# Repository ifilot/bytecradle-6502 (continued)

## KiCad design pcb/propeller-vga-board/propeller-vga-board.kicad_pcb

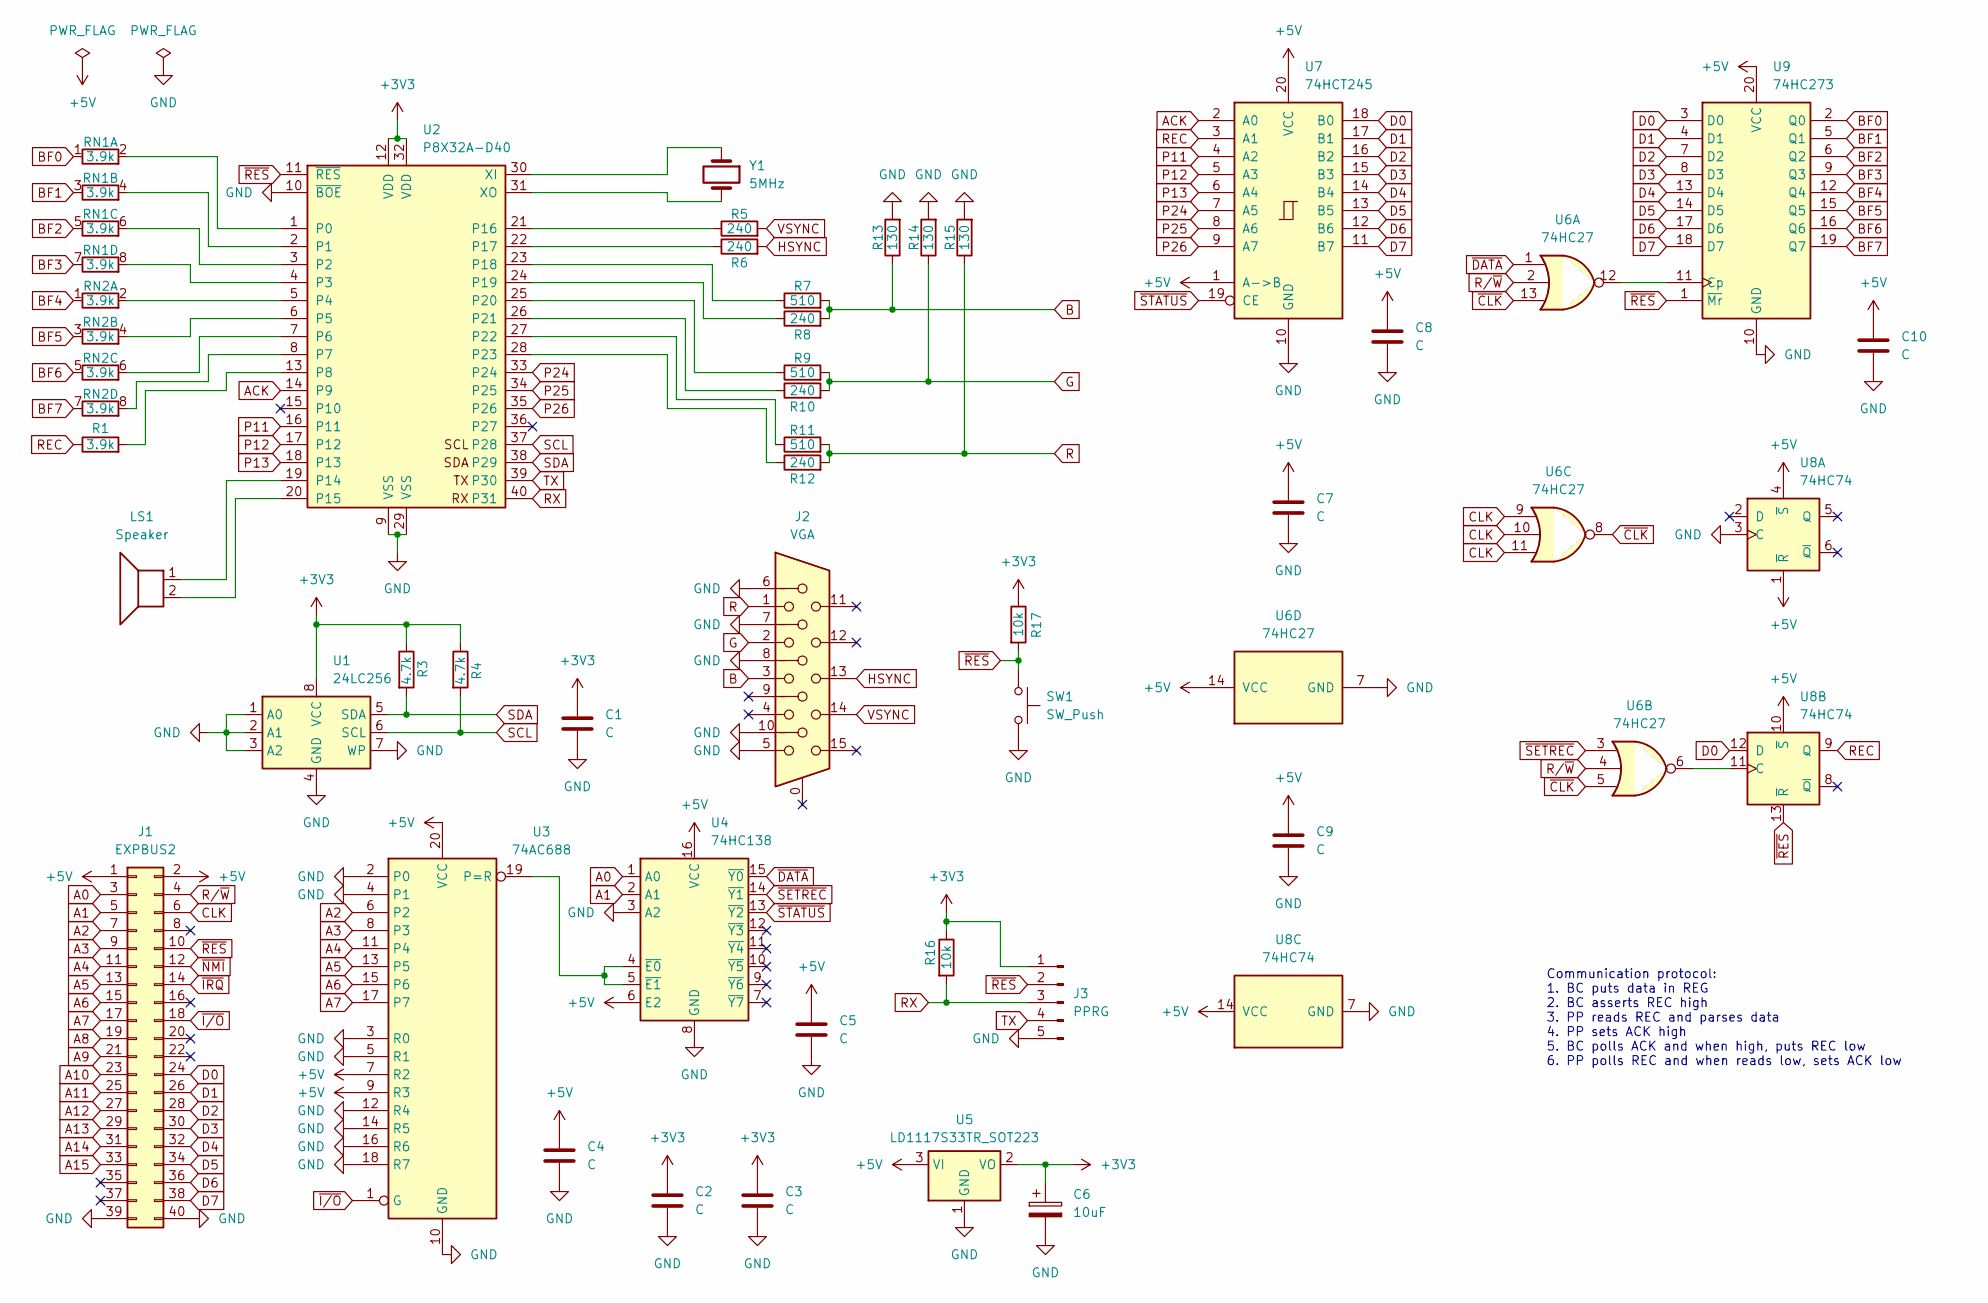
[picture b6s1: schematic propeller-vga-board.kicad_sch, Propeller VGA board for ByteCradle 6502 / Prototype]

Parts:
C1, C2, C3, C4, C5, C7, C8, C9, C10: C; C_Disc_D5.0mm_W2.5mm_P5.00mm
C6: 10uF; CP_Radial_D5.0mm_P2.50mm
J1: EXPBUS2; PinSocket_2x20_P2.54mm_Horizontal
J2: VGA; 618015330923
J3: PPRG; PinSocket_1x05_P2.54mm_Vertical
LS1: Speaker; MagneticBuzzer_ProSignal_ABI-009-RC
R1: 3.9k; R_Axial_DIN0207_L6.3mm_D2.5mm_P7.62mm_Horizontal
R3, R4: 4.7k; R_Axial_DIN0207_L6.3mm_D2.5mm_P7.62mm_Horizontal
R5, R6, R8, R10, R12: 240; R_Axial_DIN0207_L6.3mm_D2.5mm_P7.62mm_Horizontal
R7, R9, R11: 510; R_Axial_DIN0207_L6.3mm_D2.5mm_P7.62mm_Horizontal
R13, R14, R15: 130; R_Axial_DIN0207_L6.3mm_D2.5mm_P7.62mm_Horizontal
R16, R17: 10k; R_Axial_DIN0207_L6.3mm_D2.5mm_P7.62mm_Horizontal
RN1, RN2: 3.9k; R_Array_SIP8
SW1: SW_Push; SW_PUSH_6mm
U1: 24LC256; DIP-8_W7.62mm_Socket
U2: P8X32A-D40; DIP-40_W15.24mm_Socket
U3: 74AC688; DIP-20_W7.62mm_Socket
U4: 74HC138; DIP-16_W7.62mm_Socket
U5: LD1117S33TR_SOT223; SOT-223-3_TabPin2
U6: 74HC27; DIP-14_W7.62mm_Socket
U7: 74HCT245; DIP-20_W7.62mm_Socket
U8: 74HC74; DIP-14_W7.62mm_Socket
U9: 74HC273; DIP-20_W7.62mm_Socket
Y1: 5MHz; Crystal_HC49-4H_Vertical

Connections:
+3V3: C1.1, C2.1, C3.1, C6.1, J3.1, R3.1, R4.1, R16.1, R17.1, U1.8 (VCC), U2.12 (VDD), U2.32 (VDD), U5.2 (VO)
+5V: C4.1, C5.1, C7.1, C8.1, C9.1, C10.1, J1.1, J1.2, U3.7 (R2), U3.9 (R3), U3.20 (VCC), U4.6 (E2), U4.16 (VCC), U5.3 (VI), U6.14 (VCC), U7.1 (A->B), U7.20 (VCC), U8.1 (~R), U8.4 (~S), U8.10 (~S), U8.14 (VCC), U9.20 (VCC)
A0: J1.3, U4.1 (A0)
A1: J1.5, U4.2 (A1)
A2: J1.7, U3.6 (P2)
A3: J1.9, U3.8 (P3)
A4: J1.11, U3.11 (P4)
A5: J1.13, U3.13 (P5)
A6: J1.15, U3.15 (P6)
A7: J1.17, U3.17 (P7)
A8: J1.19
A9: J1.21
A10: J1.23
A11: J1.25
A12: J1.27
A13: J1.29
A14: J1.31
A15: J1.33
ACK: U2.14 (P9), U7.2 (A0)
B: J2.3, R7.2, R8.2, R13.1
BF0: RN1.1 (R1.1), U9.2 (Q0)
BF1: RN1.3 (R2.1), U9.5 (Q1)
BF2: RN1.5 (R3.1), U9.6 (Q2)
BF3: RN1.7 (R4.1), U9.9 (Q3)
BF4: RN2.1 (R1.1), U9.12 (Q4)
BF5: RN2.3 (R2.1), U9.15 (Q5)
BF6: RN2.5 (R3.1), U9.16 (Q6)
BF7: RN2.7 (R4.1), U9.19 (Q7)
CLK: J1.6, U6.9, U6.10, U6.11
D0: J1.24, U7.18 (B0), U8.12 (D), U9.3 (D0)
D1: J1.26, U7.17 (B1), U9.4 (D1)
D2: J1.28, U7.16 (B2), U9.7 (D2)
D3: J1.30, U7.15 (B3), U9.8 (D3)
D4: J1.32, U7.14 (B4), U9.13 (D4)
D5: J1.34, U7.13 (B5), U9.14 (D5)
D6: J1.36, U7.12 (B6), U9.17 (D6)
D7: J1.38, U7.11 (B7), U9.18 (D7)
G: J2.2, R9.2, R10.2, R14.1
GND: C1.2, C2.2, C3.2, C4.2, C5.2, C6.2, C7.2, C8.2, C9.2, C10.2, J1.39, J1.40, J2.5, J2.6, J2.7, J2.8, J2.10, J3.5, R13.2, R14.2, R15.2, SW1.1, U1.1 (A0), U1.2 (A1), U1.3 (A2), U1.4 (GND), U1.7 (WP), U2.9 (VSS), U2.10 (~BOE), U2.29 (VSS), U3.2 (P0), U3.3 (R0), U3.4 (P1), U3.5 (R1), U3.10 (GND), U3.12 (R4), U3.14 (R5), U3.16 (R6), U3.18 (R7), U4.3 (A2), U4.8 (GND), U5.1 (GND), U6.7 (GND), U7.10 (GND), U8.3 (C), U8.7 (GND), U9.10 (GND)
HSYNC: J2.13, R6.2
unnamed: RN1.2 (R1.2), U2.1 (P0)
unnamed: RN1.4 (R2.2), U2.2 (P1)
unnamed: RN1.6 (R3.2), U2.3 (P2)
unnamed: RN1.8 (R4.2), U2.4 (P3)
unnamed: RN2.2 (R1.2), U2.5 (P4)
unnamed: RN2.4 (R2.2), U2.6 (P5)
unnamed: RN2.6 (R3.2), U2.7 (P6)
unnamed: RN2.8 (R4.2), U2.8 (P7)
unnamed: R1.2, U2.13 (P8)
unnamed: LS1.1, U2.19 (P14)
unnamed: LS1.2, U2.20 (P15)
unnamed: R5.1, U2.21 (P16)
unnamed: R6.1, U2.22 (P17)
unnamed: R7.1, U2.23 (P18)
unnamed: R8.1, U2.24 (P19)
unnamed: R9.1, U2.25 (P20)
unnamed: R10.1, U2.26 (P21)
unnamed: R11.1, U2.27 (P22)
unnamed: R12.1, U2.28 (P23)
unnamed: U2.30 (XI), Y1.1
unnamed: U2.31 (XO), Y1.2
unnamed: U3.19 (P=R), U4.4 (~E0), U4.5 (~E1)
unnamed: U6.6, U8.11 (C)
unnamed: U6.12, U9.11 (Cp)
P11: U2.16 (P11), U7.4 (A2)
P12: U2.17 (P12), U7.5 (A3)
P13: U2.18 (P13), U7.6 (A4)
P24: U2.33 (P24), U7.7 (A5)
P25: U2.34 (P25), U7.8 (A6)
P26: U2.35 (P26), U7.9 (A7)
R: J2.1, R11.2, R12.2, R15.1
REC: R1.1, U7.3 (A1), U8.9 (Q)
RX: J3.3, R16.2, U2.40 (P31)
R/~W: J1.4, U6.2, U6.4
SCL: R4.2, U1.6 (SCL), U2.37 (P28)
SDA: R3.2, U1.5 (SDA), U2.38 (P29)
TX: J3.4, U2.39 (P30)
VSYNC: J2.14, R5.2
~CLK: U6.5, U6.8, U6.13
~DATA: U4.15 (~Y0), U6.1
~IRQ: J1.14
~I/O: J1.18, U3.1 (G)
~NMI: J1.12
~RES: J1.10, J3.2, R17.2, SW1.2, U2.11 (~RES), U8.13 (~R), U9.1 (~Mr)
~SETREC: U4.14 (~Y1), U6.3
~STATUS: U4.13 (~Y2), U7.19 (CE)

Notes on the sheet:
Communication protocol: 1. BC puts data in REG 2. BC asserts REC high 3. PP reads REC and parses data 4. PP sets ACK high 5. BC polls ACK and when high, puts REC low 6. PP polls REC and when reads low, sets ACK low

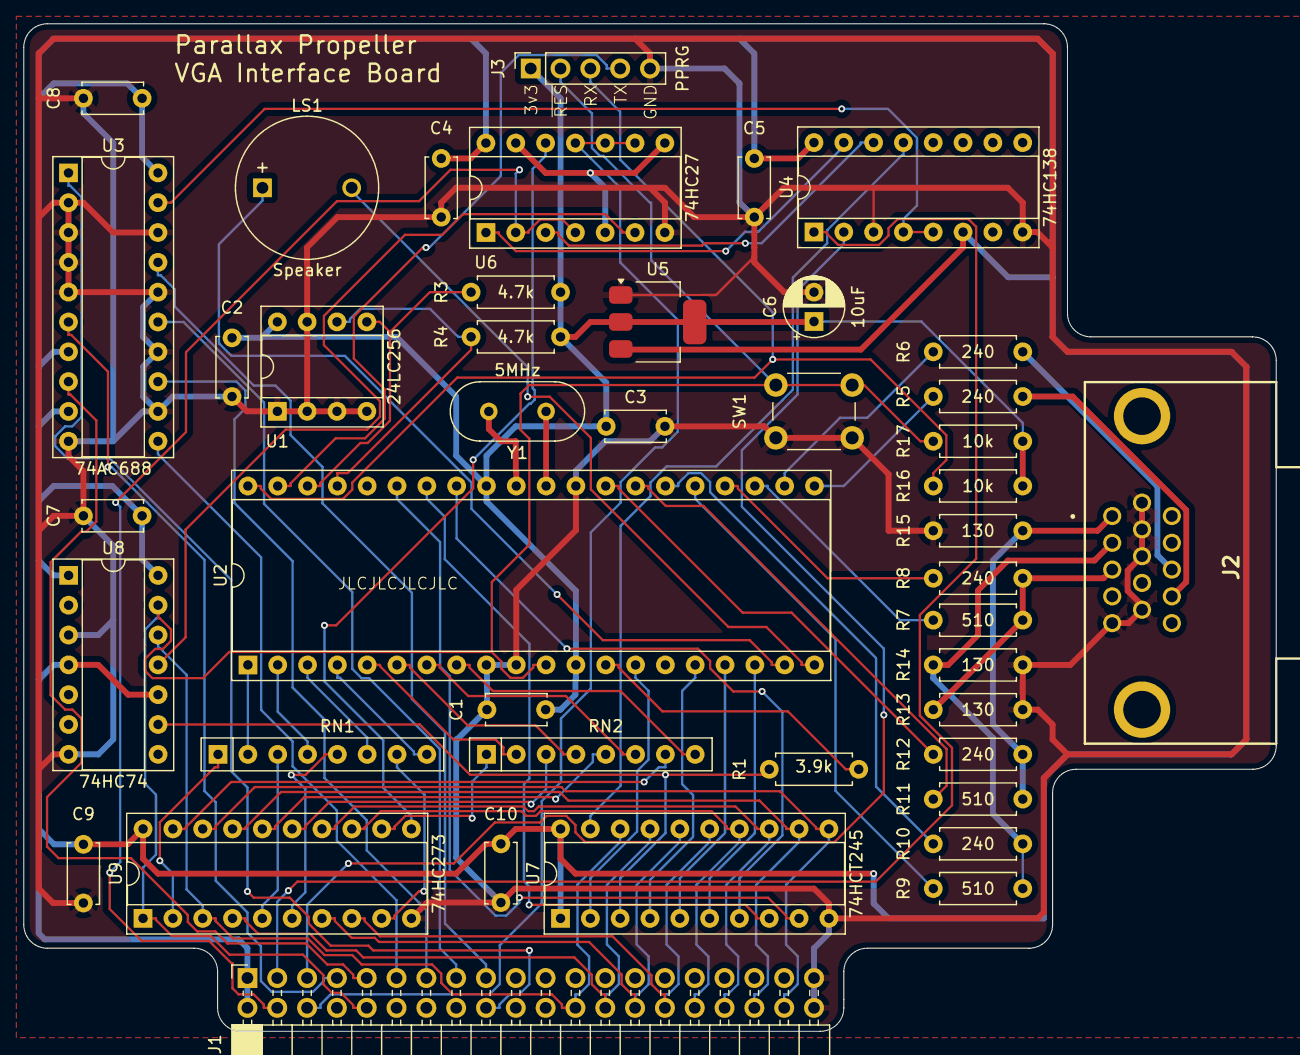
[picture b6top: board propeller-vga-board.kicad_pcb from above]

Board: 2 copper layers, 106.7 x 85.8 mm, 43 parts (0 on the bottom side), 76 nets.

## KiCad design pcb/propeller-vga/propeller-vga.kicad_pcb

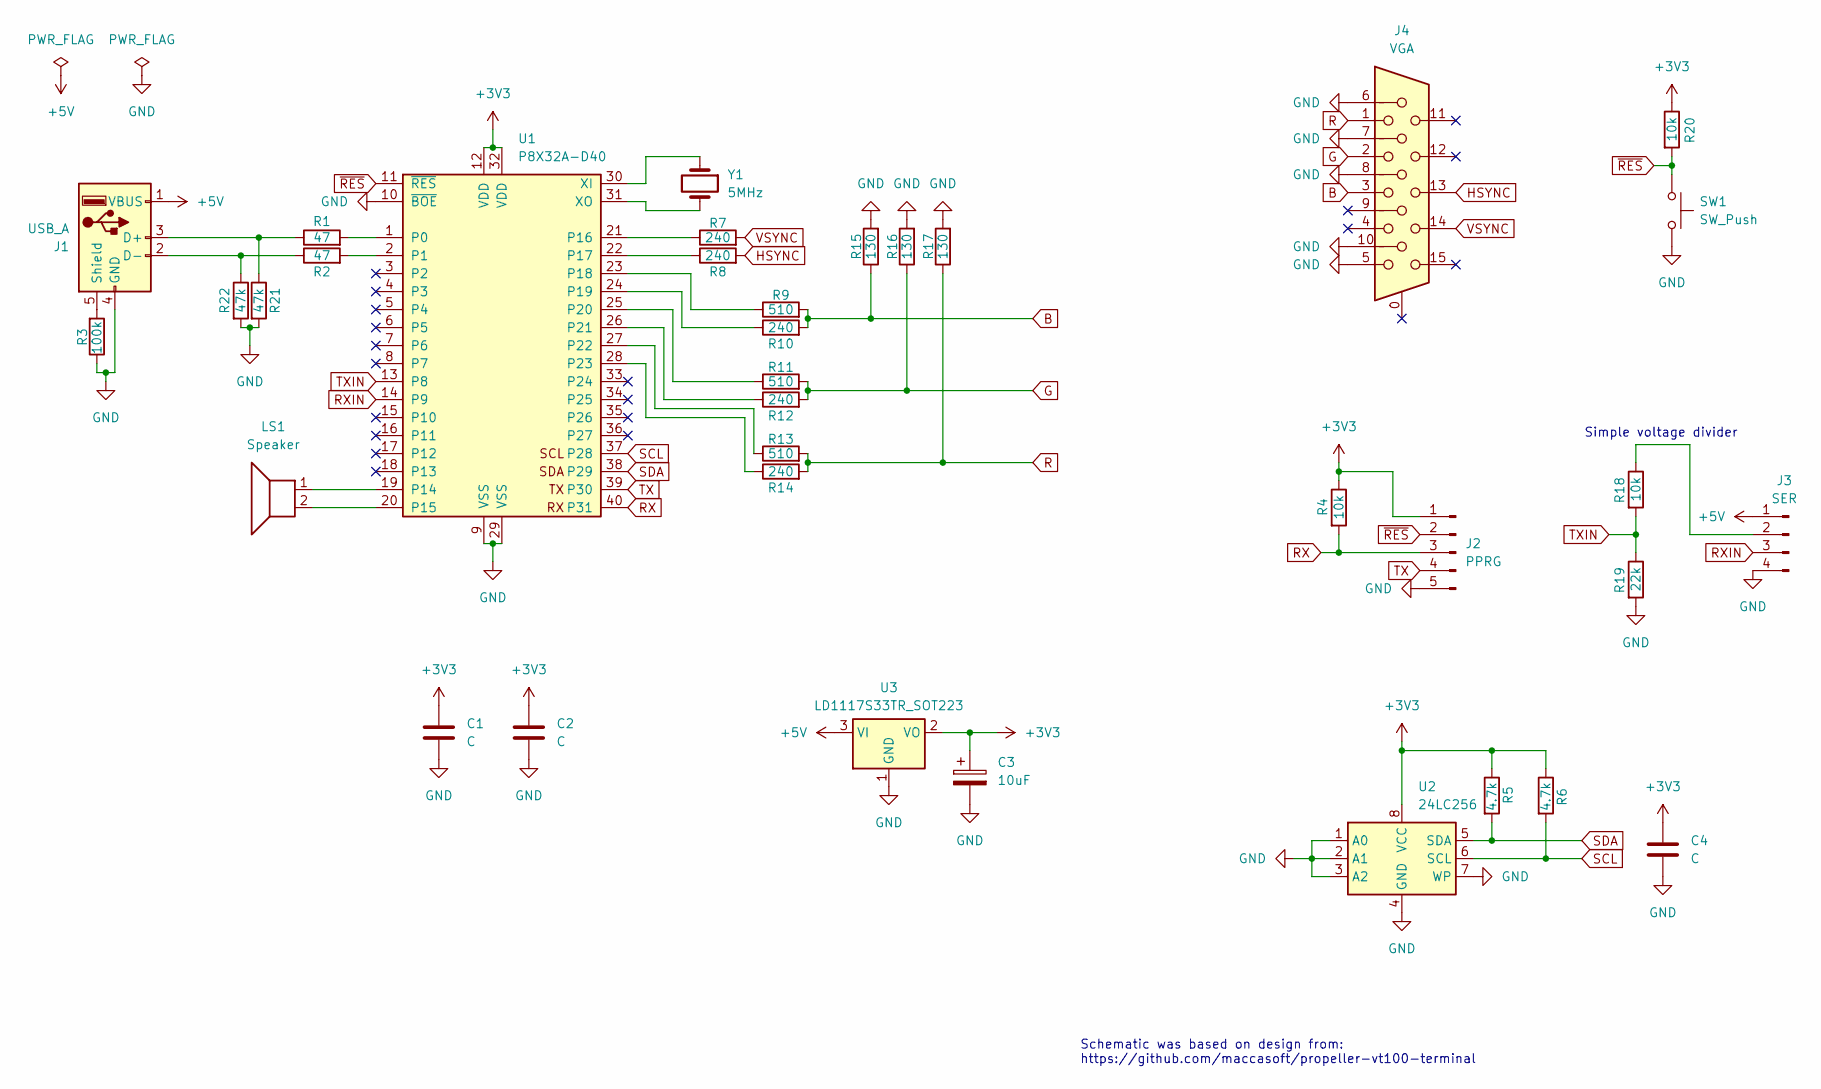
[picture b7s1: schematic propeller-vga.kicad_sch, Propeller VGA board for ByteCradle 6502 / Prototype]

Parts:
C1, C2, C4: C; C_Disc_D5.0mm_W2.5mm_P5.00mm
C3: 10uF; CP_Radial_D5.0mm_P2.50mm
J1: USB_A; USB_A_Stewart_SS-52100-001_Horizontal
J2: PPRG; PinSocket_1x05_P2.54mm_Vertical
J3: SER; PinSocket_1x04_P2.54mm_Vertical
J4: VGA; 618015330923
LS1: Speaker; MagneticBuzzer_ProSignal_ABI-009-RC
R1, R2: 47; R_Axial_DIN0207_L6.3mm_D2.5mm_P7.62mm_Horizontal
R3: 100k; R_Axial_DIN0207_L6.3mm_D2.5mm_P7.62mm_Horizontal
R4, R18, R20: 10k; R_Axial_DIN0207_L6.3mm_D2.5mm_P7.62mm_Horizontal
R5, R6: 4.7k; R_Axial_DIN0207_L6.3mm_D2.5mm_P7.62mm_Horizontal
R7, R8, R10, R12, R14: 240; R_Axial_DIN0207_L6.3mm_D2.5mm_P7.62mm_Horizontal
R9, R11, R13: 510; R_Axial_DIN0207_L6.3mm_D2.5mm_P7.62mm_Horizontal
R15, R16, R17: 130; R_Axial_DIN0207_L6.3mm_D2.5mm_P7.62mm_Horizontal
R19: 22k; R_Axial_DIN0207_L6.3mm_D2.5mm_P7.62mm_Horizontal
R21, R22: 47k; R_Axial_DIN0207_L6.3mm_D2.5mm_P7.62mm_Horizontal
SW1: SW_Push; SW_PUSH_6mm
U1: P8X32A-D40; DIP-40_W15.24mm_Socket
U2: 24LC256; DIP-8_W7.62mm_Socket
U3: LD1117S33TR_SOT223; SOT-223-3_TabPin2
Y1: 5MHz; Crystal_HC49-4H_Vertical

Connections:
+3V3: C1.1, C2.1, C3.1, C4.1, J2.1, R4.1, R5.1, R6.1, R20.1, U1.12 (VDD), U1.32 (VDD), U2.8 (VCC), U3.2 (VO)
+5V: J1.1 (VBUS), J3.1, U3.3 (VI)
B: J4.3, R9.2, R10.2, R15.1
G: J4.2, R11.2, R12.2, R16.1
GND: C1.2, C2.2, C3.2, C4.2, J1.4 (GND), J2.5, J3.4, J4.5, J4.6, J4.7, J4.8, J4.10, R3.1, R15.2, R16.2, R17.2, R19.2, R21.2, R22.2, SW1.1, U1.9 (VSS), U1.10 (~BOE), U1.29 (VSS), U2.1 (A0), U2.2 (A1), U2.3 (A2), U2.4 (GND), U2.7 (WP), U3.1 (GND)
HSYNC: J4.13, R8.2
unnamed: J1.3 (D+), R1.1, R21.1
unnamed: J1.2 (D-), R2.1, R22.1
unnamed: J1.5 (Shield), R3.2
unnamed: J3.2, R18.1
unnamed: R1.2, U1.1 (P0)
unnamed: R2.2, U1.2 (P1)
unnamed: LS1.1, U1.19 (P14)
unnamed: LS1.2, U1.20 (P15)
unnamed: R7.1, U1.21 (P16)
unnamed: R8.1, U1.22 (P17)
unnamed: R9.1, U1.23 (P18)
unnamed: R10.1, U1.24 (P19)
unnamed: R11.1, U1.25 (P20)
unnamed: R12.1, U1.26 (P21)
unnamed: R13.1, U1.27 (P22)
unnamed: R14.1, U1.28 (P23)
unnamed: U1.30 (XI), Y1.1
unnamed: U1.31 (XO), Y1.2
R: J4.1, R13.2, R14.2, R17.1
RX: J2.3, R4.2, U1.40 (P31)
RXIN: J3.3, U1.14 (P9)
SCL: R6.2, U1.37 (P28), U2.6 (SCL)
SDA: R5.2, U1.38 (P29), U2.5 (SDA)
TX: J2.4, U1.39 (P30)
TXIN: R18.2, R19.1, U1.13 (P8)
VSYNC: J4.14, R7.2
~RES: J2.2, R20.2, SW1.2, U1.11 (~RES)

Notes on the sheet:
Schematic was based on design from: https://github.com/maccasoft/propeller-vt100-terminal
Simple voltage divider

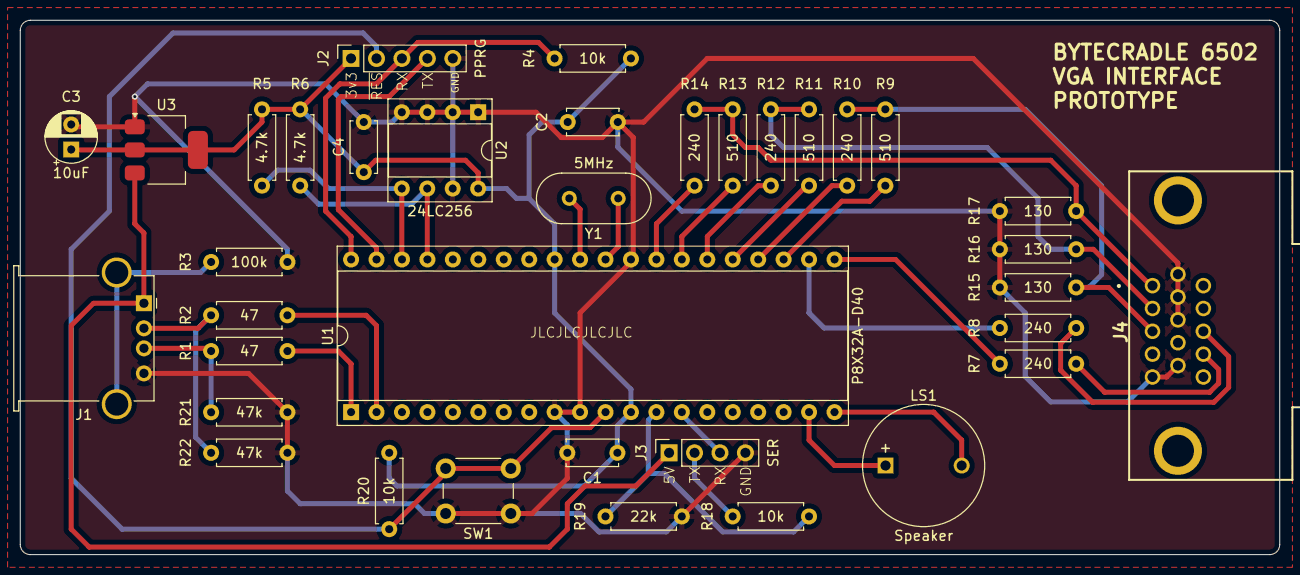
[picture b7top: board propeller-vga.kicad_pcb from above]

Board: 2 copper layers, 125.7 x 53.3 mm, 36 parts (0 on the bottom side), 33 nets.

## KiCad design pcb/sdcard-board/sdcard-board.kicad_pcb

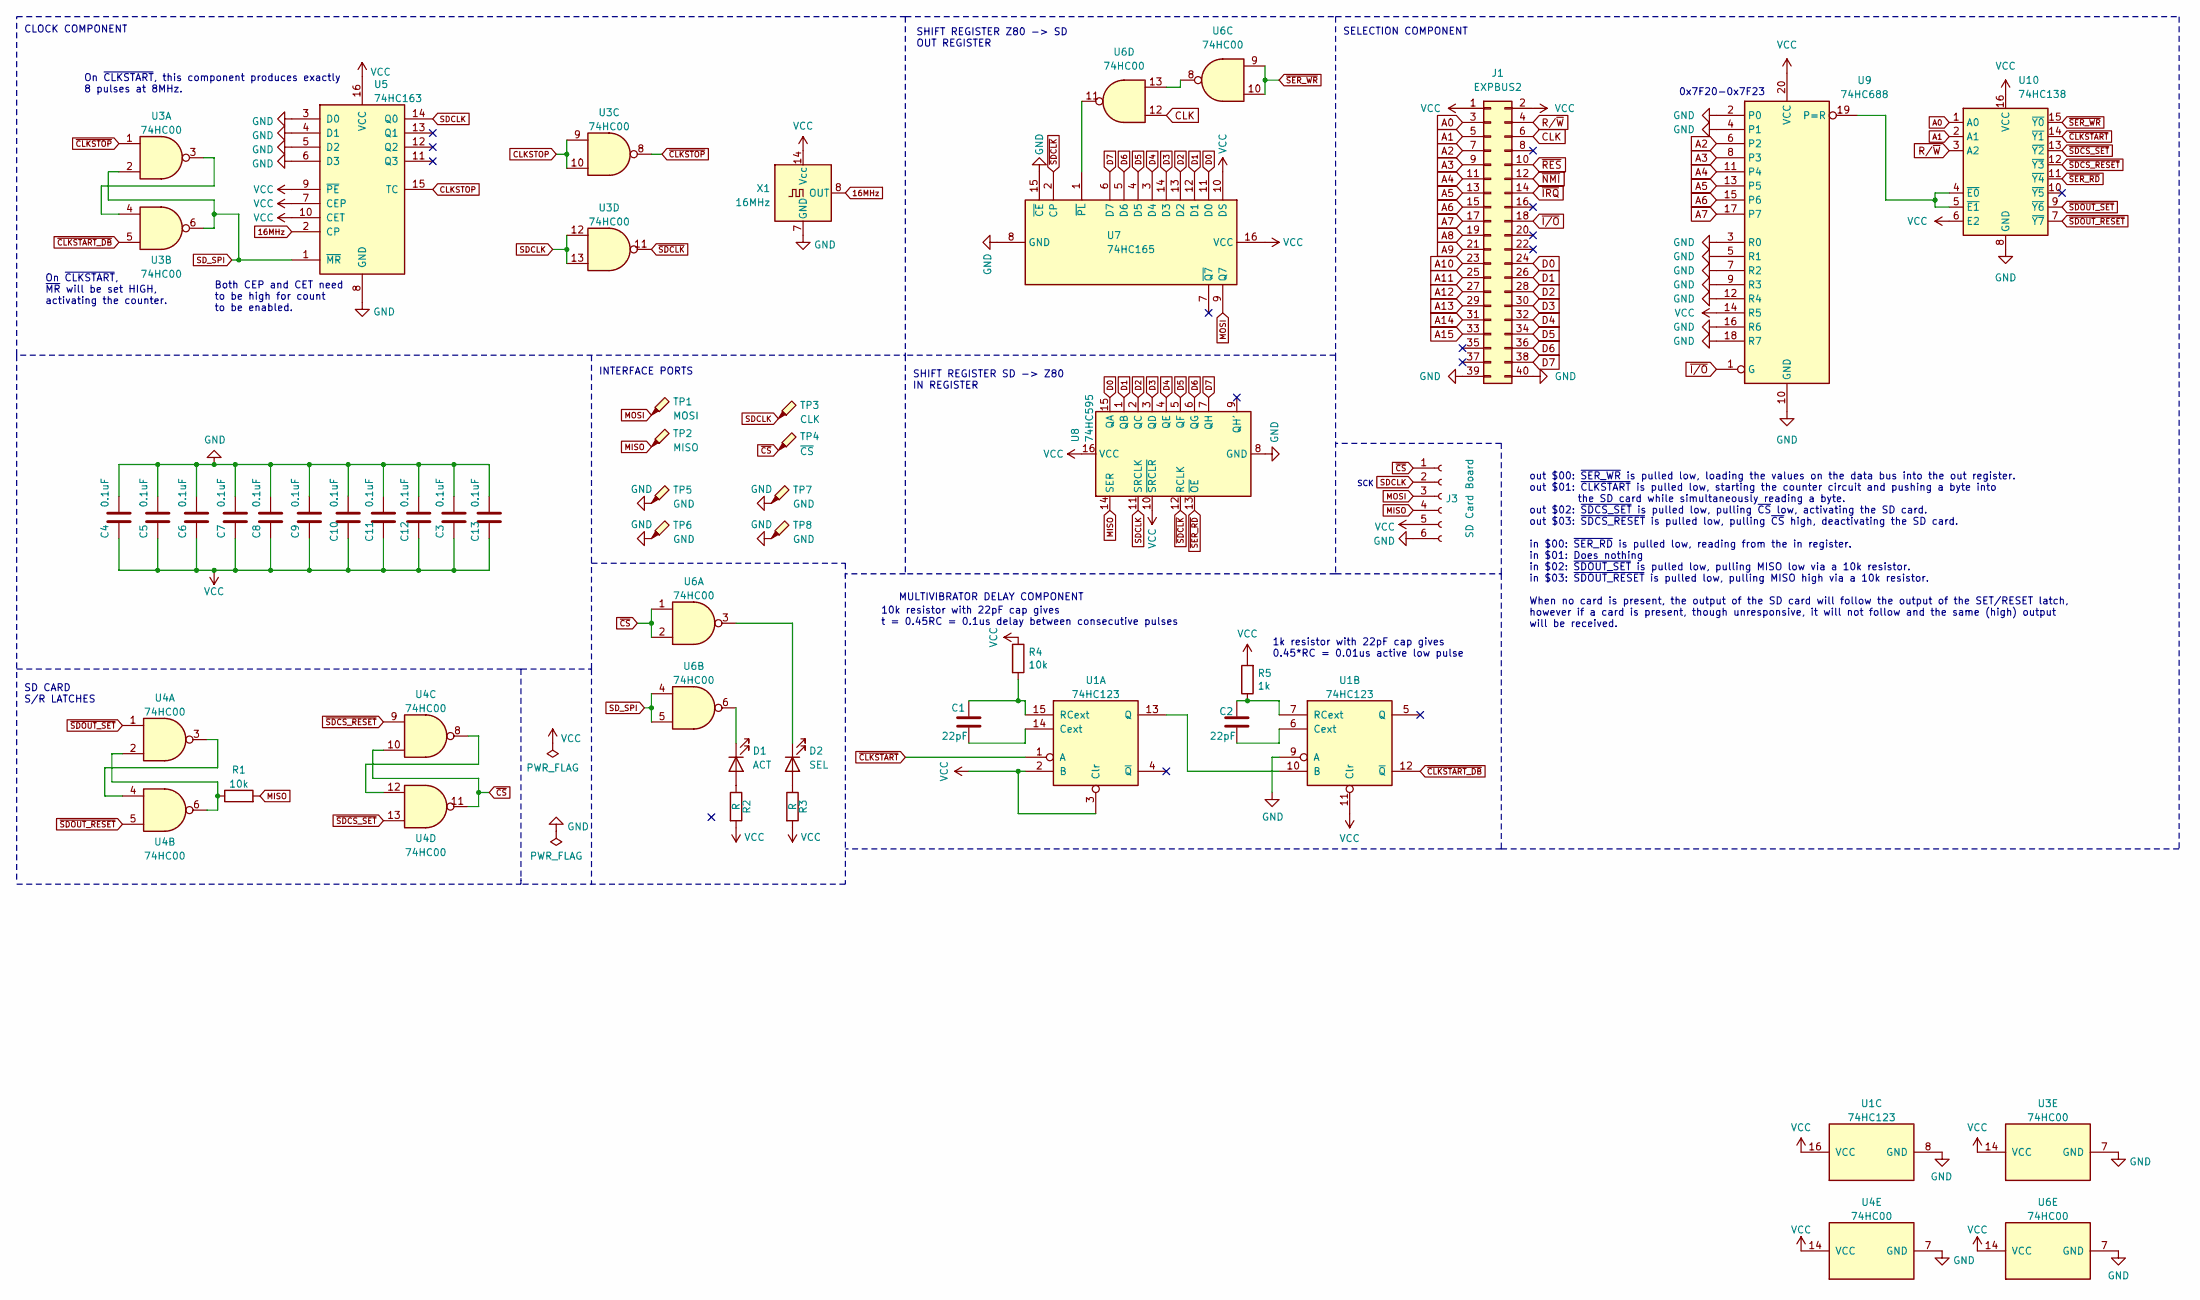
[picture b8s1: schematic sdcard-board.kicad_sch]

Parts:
C1, C2: 22pF; C_Disc_D5.0mm_W2.5mm_P5.00mm
C3, C4, C5, C6, C7, C8, C9, C10, C11, C12, C13: 0.1uF; C_Disc_D5.0mm_W2.5mm_P5.00mm
D1: ACT; LED_D5.0mm
D2: SEL; LED_D5.0mm
J1: EXPBUS2; PinSocket_2x20_P2.54mm_Horizontal
J3: SD Card Board; sdcard-socket
R1, R4: 10k; R_Axial_DIN0207_L6.3mm_D2.5mm_P7.62mm_Horizontal
R2, R3: R; R_Axial_DIN0207_L6.3mm_D2.5mm_P7.62mm_Horizontal
R5: 1k; R_Axial_DIN0207_L6.3mm_D2.5mm_P7.62mm_Horizontal
TP1: MOSI; TestPoint_THTPad_2.5x2.5mm_Drill1.2mm
TP2: MISO; TestPoint_THTPad_2.5x2.5mm_Drill1.2mm
TP3: CLK; TestPoint_THTPad_2.5x2.5mm_Drill1.2mm
TP4: ~{CS}; TestPoint_THTPad_2.5x2.5mm_Drill1.2mm
TP5, TP6, TP7, TP8: GND; TestPoint_THTPad_2.5x2.5mm_Drill1.2mm
U1: 74HC123; DIP-16_W7.62mm_Socket
U3, U4, U6: 74HC00; DIP-14_W7.62mm_Socket
U5: 74HC163; DIP-16_W7.62mm_Socket
U7: 74HC165; DIP-16_W7.62mm_Socket
U8: 74HC595; DIP-16_W7.62mm_Socket
U9: 74HC688; DIP-20_W7.62mm_Socket
U10: 74HC138; DIP-16_W7.62mm_Socket
X1: 16MHz; Oscillator_DIP-14

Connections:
16MHz: U5.2 (CP), X1.8 (OUT)
A0: J1.3, U10.1 (A0)
A1: J1.5, U10.2 (A1)
A2: J1.7, U9.6 (P2)
A3: J1.9, U9.8 (P3)
A4: J1.11, U9.11 (P4)
A5: J1.13, U9.13 (P5)
A6: J1.15, U9.15 (P6)
A7: J1.17, U9.17 (P7)
A8: J1.19
A9: J1.21
A10: J1.23
A11: J1.25
A12: J1.27
A13: J1.29
A14: J1.31
A15: J1.33
CLK: J1.6, U6.12
CLKSTOP: U3.9, U3.10, U5.15 (TC)
D0: J1.24, U7.11 (D0), U8.15 (QA)
D1: J1.26, U7.12 (D1), U8.1 (QB)
D2: J1.28, U7.13 (D2), U8.2 (QC)
D3: J1.30, U7.14 (D3), U8.3 (QD)
D4: J1.32, U7.3 (D4), U8.4 (QE)
D5: J1.34, U7.4 (D5), U8.5 (QF)
D6: J1.36, U7.5 (D6), U8.6 (QG)
D7: J1.38, U7.6 (D7), U8.7 (QH)
GND: C3.2, C4.2, C5.2, C6.2, C7.2, C8.2, C9.2, C10.2, C11.2, C12.2, C13.2, J1.39, J1.40, J3.6, TP5.1, TP6.1, TP7.1, TP8.1, U1.8 (GND), U1.9 (A), U3.7 (GND), U4.7 (GND), U5.3 (D0), U5.4 (D1), U5.5 (D2), U5.6 (D3), U5.8 (GND), U6.7 (GND), U7.8 (GND), U7.15 (~CE), U8.8 (GND), U9.2 (P0), U9.3 (R0), U9.4 (P1), U9.5 (R1), U9.7 (R2), U9.9 (R3), U9.10 (GND), U9.12 (R4), U9.16 (R6), U9.18 (R7), U10.8 (GND), X1.7 (GND)
MISO: J3.4, R1.2, TP2.1, U8.14 (SER)
MOSI: J3.3, TP1.1, U7.9 (Q7)
unnamed: D1.2 (A), R2.1
unnamed: D1.1 (K), U6.6
unnamed: D2.2 (A), R3.1
unnamed: D2.1 (K), U6.3
unnamed: R1.1, U4.2, U4.6
unnamed: C1.1, U1.14 (Cext)
unnamed: U1.10 (B), U1.13 (Q)
unnamed: C1.2, R4.2, U1.15 (RCext)
unnamed: C2.1, U1.6 (Cext)
unnamed: C2.2, R5.1, U1.7 (RCext)
unnamed: U3.3, U3.4
unnamed: U4.3, U4.4
unnamed: U4.8, U4.12
unnamed: U6.8, U6.13
unnamed: U6.11, U7.1 (~PL)
unnamed: U9.19 (P=R), U10.4 (~E0), U10.5 (~E1)
R/~W: J1.4, U10.3 (A2)
SDCLK: J3.2, TP3.1, U3.12, U3.13, U5.14 (Q0), U8.11 (SRCLK)
SD_SPI: U3.2, U3.6, U5.1 (~MR), U6.4, U6.5
VCC: C3.1, C4.1, C5.1, C6.1, C7.1, C8.1, C9.1, C10.1, C11.1, C12.1, C13.1, J1.1, J1.2, J3.5, R2.2, R3.2, R4.1, R5.2, U1.2 (B), U1.3 (Clr), U1.11 (Clr), U1.16 (VCC), U3.14 (VCC), U4.14 (VCC), U5.7 (CEP), U5.9 (~PE), U5.10 (CET), U5.16 (VCC), U6.14 (VCC), U7.10 (DS), U7.16 (VCC), U8.10 (~SRCLR), U8.16 (VCC), U9.14 (R5), U9.20 (VCC), U10.6 (E2), U10.16 (VCC), X1.14 (Vcc)
~CLKSTART_DB: U1.12 (~Q), U3.5
~CLKSTART: U1.1 (A), U10.14 (~Y1)
~CLKSTOP: U3.1, U3.8
~CS: J3.1, TP4.1, U4.10, U4.11, U6.1, U6.2
~IRQ: J1.14
~I/O: J1.18, U9.1 (G)
~NMI: J1.12
~RES: J1.10
~SDCLK: U3.11, U7.2 (CP), U8.12 (RCLK)
~SDCS_RESET: U4.9, U10.12 (~Y3)
~SDCS_SET: U4.13, U10.13 (~Y2)
~SDOUT_RESET: U4.5, U10.7 (~Y7)
~SDOUT_SET: U4.1, U10.9 (~Y6)
~SER_RD: U8.13 (~OE), U10.11 (~Y4)
~SER_WR: U6.9, U6.10, U10.15 (~Y0)

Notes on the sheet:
SHIFT REGISTER SD -> Z80 IN REGISTER
SD CARD S/R LATCHES
out $00: ~{SER_WR} is pulled low, loading the values on the data bus into the out register. out $01: ~{CLKSTART} is pulled low, starting the counter circuit and pushing a byte into the SD card while simultaneously reading a byte. out $02: ~{SDCS_SET} is pulled low, pulling ~{CS} low, activating the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
On ~{CLKSTART}, this component produces exactly 8 pulses at 8MHz.
On ~{CLKSTART}, ~{MR} will be set HIGH, activating the counter.
in $00: ~{SER_RD} is pulled low, reading from the in register. in $01: Does nothing in $02: ~{SDOUT_SET} is pulled low, pulling MISO low via a 10k resistor. in $03: ~{SDOUT_RESET} is pulled low, pulling MISO high via a 10k resistor. When no card is present, the output of the SD card will follow the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
0x7F20-0x7F23
SELECTION COMPONENT
1k resistor with 22pF cap gives 0.45*RC = 0.01us active low pulse
10k resistor with 22pF cap gives t = 0.45RC = 0.1us delay between consecutive pulses
CLOCK COMPONENT
INTERFACE PORTS
Both CEP and CET need to be high for count to be enabled.
SCK
MULTIVIBRATOR DELAY COMPONENT
SHIFT REGISTER Z80 -> SD OUT REGISTER

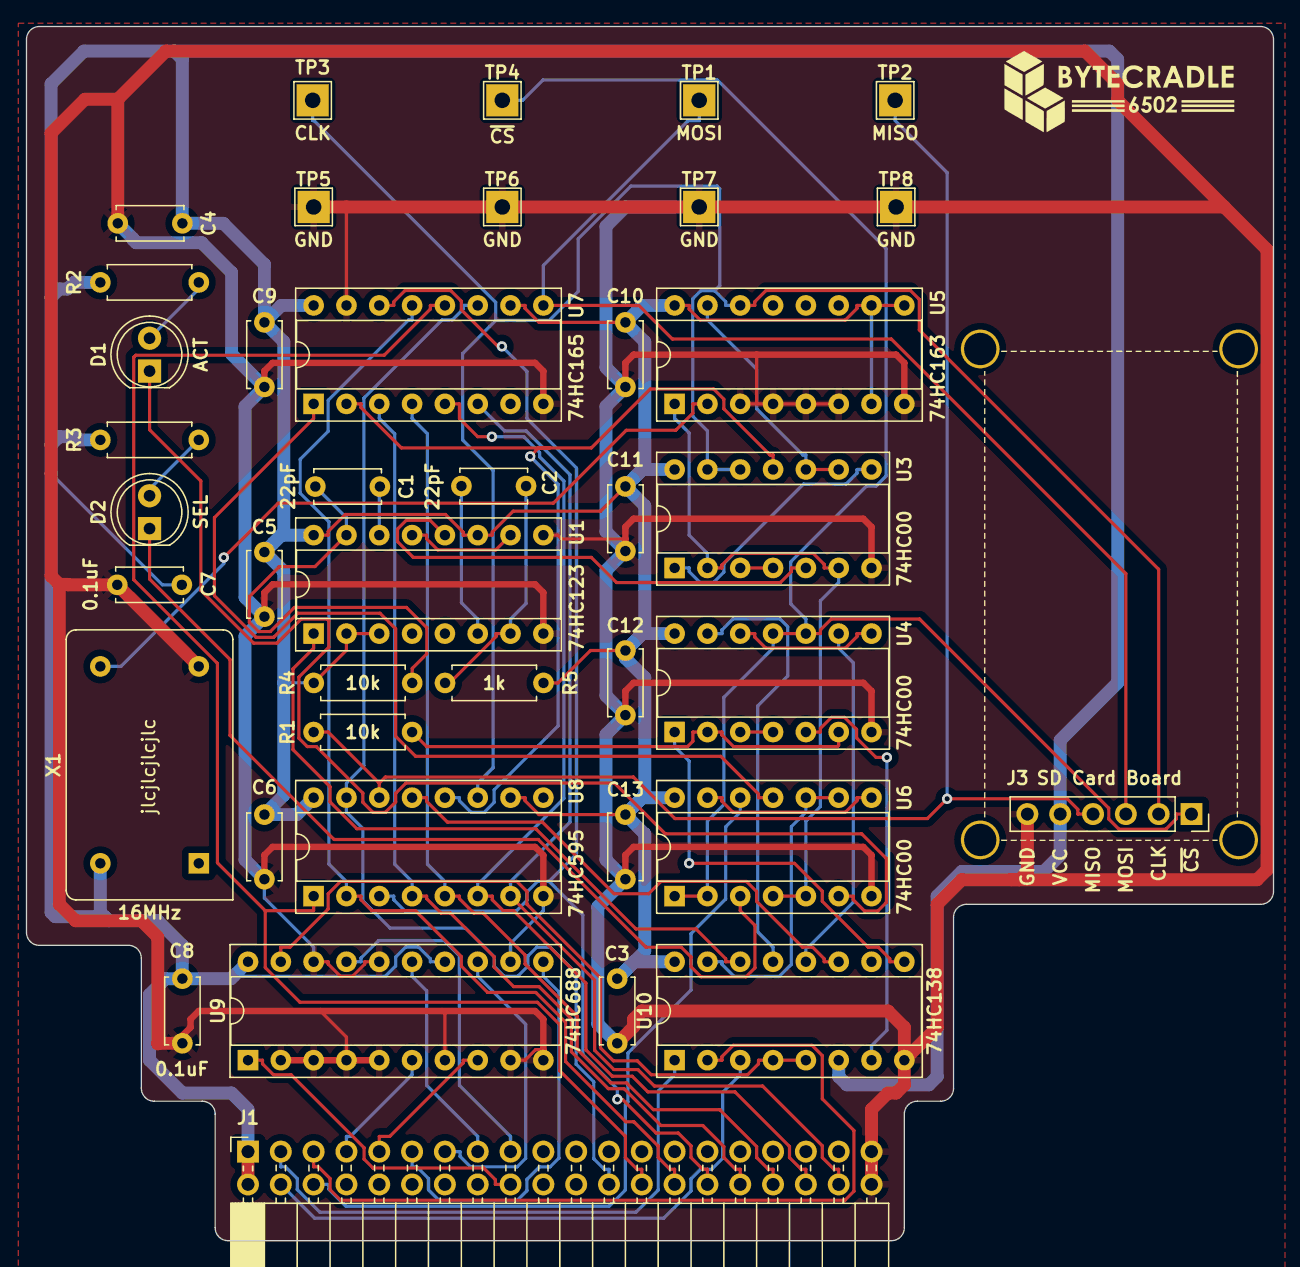
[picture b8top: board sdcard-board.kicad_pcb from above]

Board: 2 copper layers, 96.5 x 94.0 mm, 40 parts (0 on the bottom side), 54 nets.

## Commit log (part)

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2025-02-05 Further polishing assembler
2025-02-07 Refactoring code, fixing bugs in putdec and assembly routines
2025-02-07 Adding documentation
2025-02-07 deploy: 4aa076f7ac4b08007040f9c570fafe9bf50197dd
2025-02-07 Rewriting README.md
2025-02-07 deploy: fee028e5915f49c5dc85fb5d4f89fdb8e31840d1
2025-02-07 Adding shield badge
2025-02-07 Updating logos
2025-02-07 deploy: 573d50bad3c9ab926f46a6ecf29022f1bf90f857
2025-02-07 Modifying docs
2025-02-07 deploy: c72619f1056a6c69f65a5956b42645effdf2a012
2025-02-07 Inserting documentation placeholders
2025-02-07 deploy: 140ee7131eaf9600e69500956e4bfad12b3d64fb
2025-02-07 Adding VGA interface prototype
2025-02-08 Updating schematic
2025-02-09 Updating design for V2
2025-02-09 Modifying monitor routines for rev2 board
2025-02-09 Initial commit SD-card routines
2025-02-09 Making some adjustments in SD-card routines
2025-02-10 Polishing SD-card routines
2025-02-10 Reading boot sector of SD-card
2025-02-11 Small tweaks to IO and SD routines
2025-02-11 Adjusting SD card routines
2025-02-14 Fixing a few bugs and adding test routines
2025-02-15 Fixing putdec algorithm
2025-02-15 Fixing a few bugs, bug in assembler still remaining
2025-02-15 Decreasing CPU speed to 4MHz
2025-02-15 Fixing bugs
2025-02-15 Updating documentation
2025-02-15 deploy: a71a386bdc704504a3385e2dcba49e720e084645
2025-02-15 Fixing minor bug in disassembler
2025-02-15 Improving monitor routines
2025-02-15 Initial commit OS
2025-02-15 Fixing OS routines
2025-02-15 Removing lib file
2025-02-15 Adding SD card to emulator
2025-02-16 Trying to implement SD card routines in C
2025-02-16 Refactoring code
2025-02-16 EOW commit requiring pointer to inc2sp
2025-02-16 Migrating SD card routines to C
2025-02-16 Refactoring source
2025-02-16 Creating compatible routine
2025-02-16 Refactoring
2025-02-16 Multiple login attempts to connect to SD-card
2025-02-16 Polishing
2025-02-16 Relocating source code and expanding emulator
2025-02-16 Trying to read FAT
2025-02-17 Fixing image creation
2025-02-21 Initial commit readin gout directory
2025-02-21 deploy: 3aaa4ae090d9597c4fe469b4165534f47f4da0a0
2025-02-21 Implementing folder reading routines
2025-02-21 Creating Makefile
2025-02-22 Fixing file listing loop
2025-02-22 deploy: aa59ac54dcac47c5a28bb0b9295919e5ea222131
2025-02-22 Adding GPU prototype board
2025-02-22 deploy: aa33d4ccbc9db2fbc037e7b22907b32c1dc932bb
2025-02-22 Refining VGA board
2025-02-22 Removing bitpin
2025-02-23 Adding RAM banking to emulator
2025-02-23 deploy: abed48ad15f956db9927d48e515d1564046d32b8
2025-02-23 Adding memory test
2025-02-23 Adding file finding routine
2025-02-23 deploy: 0a14122631ff759af2281310d049acd678a121da
2025-02-23 Adding testhat for VGA via Parallax Propeller
2025-02-23 Adding file loading function
2025-02-28 Initial commit command parsing routines
2025-02-28 Adding change directory functionality
2025-02-28 Implementing file reading
2025-02-28 Trying to implement .COM execution
2025-03-01 Launching programs from command line
2025-03-01 Implementing loading of external C and ASM programs
2025-03-01 Removing obsolete programs
2025-03-01 Not storing lib files
2025-03-01 Adding Github actions
2025-03-01 Fixing Makefile
2025-03-01 Updating README.md
2025-03-01 Refactoring system monitor
2025-03-02 Adding quit command to monitor
2025-03-02 Adding hexdump command
2025-03-02 Creating fast execution mode
2025-03-02 Adding mandelbrot set generator
2025-03-02 Creating simple test program
2025-03-06 Integrating NCURSES into emulator
2025-03-06 deploy: c7b444801ccba57d6632747da4459e2b07e6acde
2025-03-06 Making some further changes
2025-03-25 Saving tiny board design
2025-03-28 Revising TINY board and creating test ROM for TINY board
2025-03-29 Initial commit number routines
2025-03-30 Removing .o files and implementing printdecword routine
2025-03-30 Replacing with putspace
2025-03-30 Further work on sieve
2025-03-30 Completing sieve
2025-03-30 Speeding up code
2025-03-31 Revising single board layout
2025-03-31 Routing
2025-03-31 Initial commit bitbang SD-card routines
2025-04-01 Fixing bitbanged SD-card SPI protocol
2025-04-01 Cleaning repository and completing SD-card reading using bitbang SPI
2025-04-04 Initial commit microchess code
2025-04-04 Reformatting code
2025-04-12 Revising TINY board and writing CUPL
2025-04-12 Integrating monitor
2025-04-12 deploy: 4d74367bd6c9d07b125557e97a441a5bae42a7de
2025-04-15 Creating testrom for SBC
2025-04-19 Integrating CIA CPLD for tiny board
2025-04-19 Revising board and integrating DS1813
2025-04-23 Expanding README.md
2025-04-23 Changing source
2025-04-23 Removing link to manual (still incomplete)
2025-04-25 Initial commit revision emulator
2025-04-25 Fixing input/output
2025-04-25 Adding clock routine
2025-04-26 Integrating ACIA into emulator
2025-04-26 Adding VIA chip
2025-04-26 Adding SD-card interface
2025-04-26 Implementing SD-card in emulator and creating mini board testrom
2025-04-26 Fixing error in GA
2025-04-26 Fixing capitalization in headers
2025-04-26 Adding headers
2025-04-26 Adding dependency
2025-04-26 Hooking minirom to emulator
2025-04-26 Complete overhaul of emulator (#1)
    * Initial commit revision emulator
    * Fixing input/output
    * Adding clock routine
    * Integrating ACIA into emulator
    * Adding VIA chip
    * Adding SD-card interface
2025-04-27 Replacing docs environment
2025-04-27 deploy: 45e63a3a55e8b72749372753f313edd59a607bb8
2025-04-27 Creating placeholders for documentation
2025-04-27 Expanding documentation
2025-04-28 Fixing position hole
2025-04-28 Fixing deployment path
2025-04-28 deploy: 5a5ffb5c759afe99f7e3579c06b1cce15d034f0a
2025-04-28 Expanding documentation and fixing bugs description in assembler
2025-04-28 deploy: dc3190acefd02cdd797342f7950fc6def788c8b2
2025-04-28 tinyrom build
2025-04-28 Adding event
2025-04-28 Adding git
2025-04-28 Adjusting Makefile
2025-04-28 Further adjusting Makefile
2025-04-28 Changing GA
2025-04-28 Further revising build.yml
2025-04-28 Adding enclosure
2025-04-29 Expanding documentation and adding CUPL for mini board
2025-04-29 deploy: 1216ae2375bcd95c23e7b8c0a4377bfc31b1626b
2025-04-29 Adding boilerplate code
2025-04-29 Removing object files
2025-04-29 Revising code
2025-04-29 Fixing bugs in monitor
2025-04-29 deploy: 5b00bdd9bc07d4da4bae96438908b6bf6cf4b822
2025-04-29 Refactoring menu
2025-04-29 Polishing Makefile
2025-04-30 Initial commit ANSI test
2025-04-30 Implementing cursor placement
2025-04-30 deploy: a9c41534d38d95a64d24e5563b381c829ce682c2
2025-04-30 deploy: c75019a8af448da8ce2d4b93dca67a4f2a0a2f00
2025-04-30 deploy: 8132e13d912945e28168365041c6bf39d460a397
2025-05-01 Expanding tutorials and fixing a few functions
2025-05-01 deploy: 78a54ecebc0b4858b1af0acc7beb5680ce058edb
2025-05-01 Making small changes in bcos and minirom
2025-05-01 Revising tinyboard (REV2) and adding daughterboard with LEDs
2025-05-01 deploy: db0163fdcb2a4be4af99d20a201cd77ea26eb6ae
2025-05-02 Fixing bugs in CUPL
2025-05-02 deploy: 96469926c885a9fa4e0fdfc206fe7e11fa95e06d
2025-05-02 Initial commit miniboard revision
2025-05-03 Fixing bugs in CPLD and removing minimalistic testrom
2025-05-03 Implementing banking in emulator
2025-05-03 Fixing bugs in emulator and in Cnewline output of miniboard software
2025-05-03 Pre-fourlayerboard commit
2025-05-03 Adding documentation to schematics
2025-05-03 Exporting pages
2025-05-03 Rivising board
2025-05-03 Storing GERBERS
2025-05-03 deploy: 15e41cb7171ad6c859f1a5131f89f246dcf731b1
2025-05-03 Rewriting BCOS
2025-05-04 Polishing SD-CARD routines for revised MINI board
2025-05-04 deploy: 879630db5c4c5f16511ec3d9ceca7299dc413477
2025-05-04 Expanding schematics
2025-05-04 deploy: 55b0f5af1d1c020024ca949040417801d6927ce3
2025-05-04 Adding debug functions to emulator
2025-05-04 Implementing CRC16 checksum on SD-CARD interfacing
2025-05-04 Fixing Mandelbrot program and tuning routines
2025-05-04 Integrating optimized CRC16 checksum code using look-up table
2025-05-05 Fixing width of VIN
2025-05-05 deploy: b2b5fbe84279d6666bcc8d76399ed459f681f188
2025-05-09 Adding 10k resistor to IRQ51
2025-05-09 deploy: b6fb2544f169229ab92f69b20fa7aea52e92e077
2025-05-10 deploy: 979c88a61bebb7b1a6a9004e20d72118ca1fc07d
2025-05-10 Making small changes to tiny board and updating documentation
2025-05-10 deploy: 54f9f9ed15d01ded3ace42b248b57c40842c9f01
2025-05-10 Updating schematics
2025-05-10 Improving borard rendering
2025-05-10 Changing picture
2025-05-10 Styling board
2025-05-10 Expanding documentation and improving graphics
2025-05-10 deploy: 58ff5da477cf474c82ffa0d1846f589f6870539c
2025-05-10 Fixing links
2025-05-10 deploy: 035c8f3a239dd919919d2768f2e996158b743f15
2025-05-10 Fixing image links
2025-05-10 deploy: e501fa77702aec2927beccd85fe90fccb07317dc
2025-05-10 deploy: 7b82fb99379b80c53fafafd415134f5475e89831
2025-05-10 Adding image
2025-05-10 deploy: 6884b3b60098b73ce285f5a07ba1b732bcafccf8
2025-05-10 Updating image
2025-05-10 deploy: 0cbf1c8ddcf5fdb94b7a505d7cee53faf19ae85c
2025-05-11 Adding tutorials and explanation on program deployment
2025-05-11 deploy: 103de06cf21766a5772eb096c1ca0b1ce2190084
2025-05-11 Fixing programs
2025-05-11 Updating links
2025-05-11 deploy: b6e6ea28353ae5302231839d44c4ce28a919c970
2025-05-11 deploy: 54f60dea2e83bbe4e1b1c352b7e8e08668a539ab
2025-05-11 deploy: 408bb7651e1e90014d5dce6d56c3b527980dc4bc
2025-05-11 Adding datasheets
2025-05-11 deploy: 59df9b51e8433b7304fc5f4958ff25cf7ee0a04e
2025-05-11 Fixing links and tuning CSS
2025-05-11 deploy: 15bc1cf1fa895e9d25aa80c6e0674936d4b459c4
2025-05-12 Exposing BCOS ROM and modifying README file
2025-05-12 deploy: 883eba5585ce94bad29478d2a56069d4e4721f43
2025-05-12 Adding hardware customization for ACIA
2025-05-12 deploy: b1a4a874088d362ff091d3c8228491705a73a20d
2025-05-12 Adding comments
2025-05-12 deploy: 426f63ac8404eda95a87f845a5ebeeef55eb309e
2025-05-14 Adding a delay routine
2025-05-14 deploy: 1ba0123a8154f9acff1bdd9ce4930840770d374d
2025-05-14 Implementing blinkenlight
2025-05-15 adding spigot
2025-05-18 Adding strobe
2025-05-18 deploy: 2259e1e7c50dee553c18d07efeadf2fcdf0dcae5
2025-05-30 updated pispigot
2025-05-30 deploy: c70396703fe82808b537f373f5ff832ffc88a28c
2025-06-04 conways game of life
2025-06-28 Adjusting board for FPGA daughterboard
2025-06-28 deploy: f369c680ff344a69e294e46ff88870e204afd585
2025-09-30 Game of life with added features, and fixed spelling mistakes
2026-04-06 Fixing bugs in jumptable
2026-04-06 Reorganizing repo
2026-04-06 Adding CTRL+C and CTRL+D to exit emulator
2026-04-06 Refactoring programs
2026-04-06 deploy: 69e09f9c8f074a42e3435ba0348922e2cc26d796
2026-04-06 Updating README and names
